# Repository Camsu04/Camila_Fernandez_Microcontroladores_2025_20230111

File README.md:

# Camila_Fernandez_Microcontroladores_2025_Mecatronic
Asignaciones &amp; Proyectos de Microcontroladores

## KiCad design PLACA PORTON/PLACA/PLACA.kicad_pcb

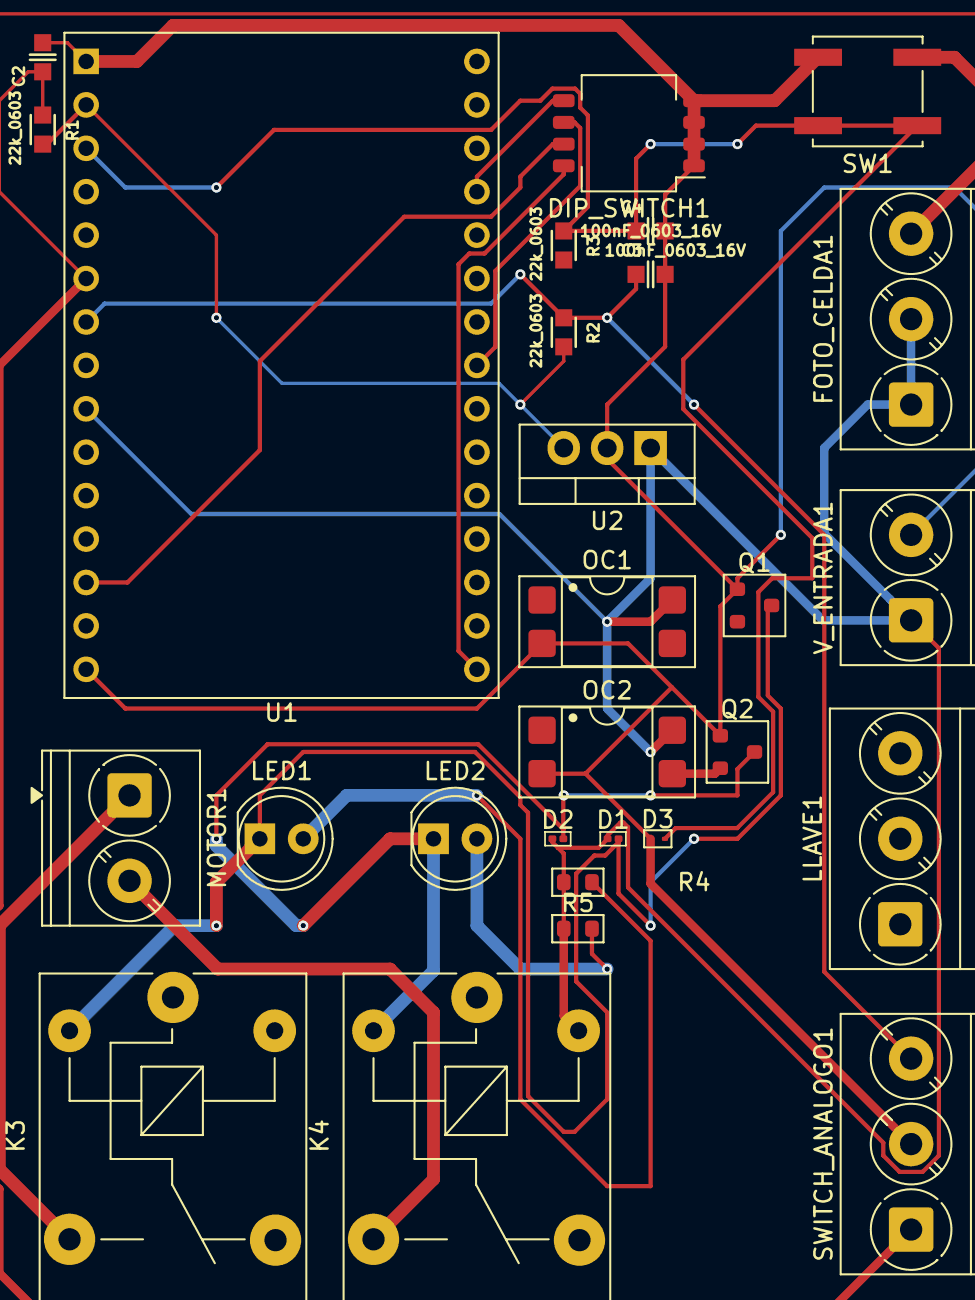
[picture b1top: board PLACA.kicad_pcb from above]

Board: 2 copper layers, 28 parts (0 on the bottom side), 20 nets.

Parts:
C2, C3, C4: 100nF_0603_16V; C_0603
D1, D2: 1N914BWS; D_0201_0603Metric_TVS
D3: ESD9B3.3; D_SOD-923_TVS
DIP_SWITCH1: SW_DIP_x04; SW_DIP_SPSTx04_Slide_KingTek_DSHP04TS_W7.62mm_P1.27mm
FOTO_CELDA1: Screw_Terminal_01x03; TerminalBlock_Phoenix_PT-1,5-3-5.0-H_1x03_P5.00mm_Horizontal
K3, K4: SANYOU_SRD_Form_C; Relay_SPDT_SANYOU_SRD_Series_Form_C
LED1, LED2: LED_0603_Red; LED_D5.0mm
LLAVE1: Screw_Terminal_01x03; TerminalBlock_Phoenix_PT-1,5-3-5.0-H_1x03_P5.00mm_Horizontal
MOTOR1: -; TerminalBlock_Phoenix_PT-1,5-2-5.0-H_1x02_P5.00mm_Horizontal
OC1, OC2: PC817; DIP-4_W7.62mm_SMDSocket_SmallPads
Q1, Q2: 2N2219; SOT-23
R1, R2, R3: 22k_0603; R_0603
R4, R5: 2k; R_0603_1608Metric
SW1: SW_Push; SW_Push_1P1T_NO_CK_KSC7xxJ
SWITCH_ANALOGO1: Screw_Terminal_01x03; TerminalBlock_Phoenix_PT-1,5-3-5.0-H_1x03_P5.00mm_Horizontal
U1: ESP32-WROOM-32D; ESP32-C3-DevKitM-1
U2: LM7805CT; TO-220-3_Vertical
V_ENTRADA1: 12V; TerminalBlock_Phoenix_PT-1,5-2-5.0-H_1x02_P5.00mm_Horizontal

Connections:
/BOARD/12V: D1.1 (K), D2.1 (K), FOTO_CELDA1.1, FOTO_CELDA1.2, K3.5, K4.5, OC1.4, OC2.4, R4.1, R5.1, U1.9 (IO33), U2.1 (IN), V_ENTRADA1.1
/BOARD/LS/5V: R1.1, R2.1, U1.2 (VDD), U2.3 (OUT)
/BOARD/LSA: C3.1, R2.2, SWITCH_ANALOGO1.3, U1.7 (IO35)
/BOARD/LSC: C2.1, R1.2, SWITCH_ANALOGO1.1, U1.6 (IO34)
/BOARD/MICRO/MOTOR_IZQUIERDA: OC2.1, U1.24 (IO2)
/BOARD/MICRO/RESET: C4.1, D3.2 (A), R3.2, SW1.2, U1.3 (EN)
/BOARD/MOTOR_DERECHA: K3.3, MOTOR1.1
/BOARD/MOTOR_IZQUIERDA: K4.3, MOTOR1.2
/BOARD/SW1: DIP_SWITCH1.8, U1.16 (IO13)
/BOARD/SW2: DIP_SWITCH1.7, U1.13 (IO14)
/BOARD/SW3: DIP_SWITCH1.6, U1.23 (IO15)
/BOARD/SW4: DIP_SWITCH1.5, U1.27 (IO16)
GND: C2.2, C3.2, C4.2, D3.1 (K), DIP_SWITCH1.1, DIP_SWITCH1.2, DIP_SWITCH1.3, DIP_SWITCH1.4, FOTO_CELDA1.3, OC1.2, OC2.2, Q1.1 (E), Q2.1 (E), SW1.1, SWITCH_ANALOGO1.2, U1.1 (GND), U1.15 (GND), U2.2, V_ENTRADA1.2
LINE: K3.1, K4.1
unnamed: D1.2 (A), K3.2, LED1.1 (K), Q1.3 (C)
unnamed: D2.2 (A), K4.2, LED2.1 (K), Q2.3 (C)
unnamed: LED1.2 (A), R4.2
unnamed: LED2.2 (A), R5.2
unnamed: OC1.3, Q1.2 (B)
unnamed: OC2.3, Q2.2 (B)

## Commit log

2025-02-04 Add files via upload
    Carpeta de Codigos
2025-02-06 Add files via upload
    segunda fase de la maquina de estado
2025-02-13 Add files via upload
    Aqui se arreglo El tema del Void y parpadeo hablado en la clase de hoy , aun falta ver mas pruebas sobre la maquina de estado.
2025-02-13 Update Maquina de Estado v3.c
    Arreglando algunos errores
2025-02-13 Update Maquina de Estado v3.c
    arreglando void de led de falla
2025-02-14 Update Maquina de Estado v3.c
    mas modificaciones
2025-02-14 Update Maquina de Estado v3.c
    arreglo de static
2025-02-14 Update Maquina de Estado v3.c
    correcciones
2025-02-14 Update Maquina de Estado v3.c
    correcion de declaracion
2025-02-14 Update Maquina de Estado v3.c
    quitando un comentario
2025-02-19 Add files via upload
    ESSP32-S3
2025-02-19 Update Main Maquina de estado.c
    LISTO
2025-02-19 Update Main Maquina de estado.c
    DEFINITIVO
2025-02-25 Add files via upload
    INVESTIGACIÓN
2025-03-13 Add files via upload
    PROTOTIPO 1
2025-03-20 Led
    Tarea 5
2025-03-27 Add files via upload
    LED V2
2025-04-10 Add files via upload
    PROYECTO FINAL 90%
